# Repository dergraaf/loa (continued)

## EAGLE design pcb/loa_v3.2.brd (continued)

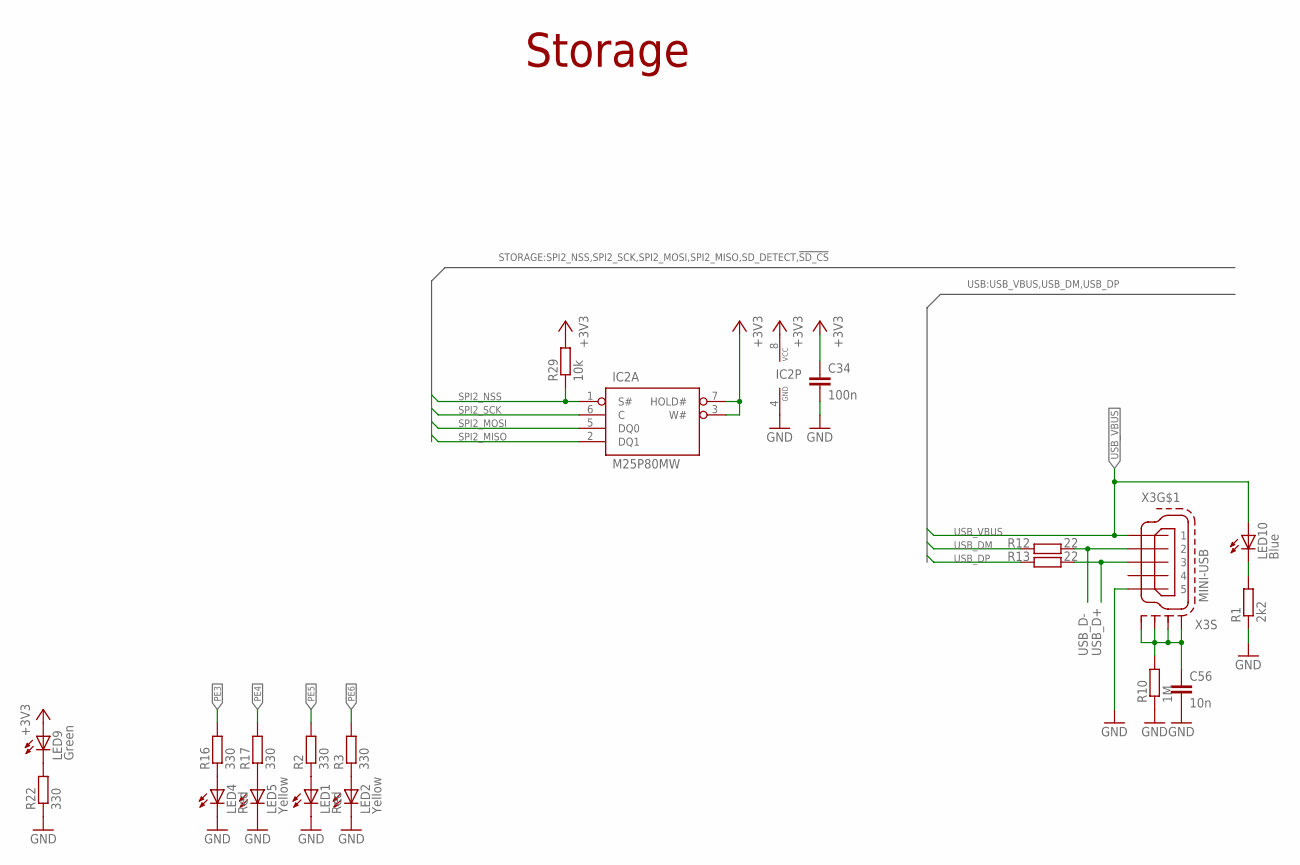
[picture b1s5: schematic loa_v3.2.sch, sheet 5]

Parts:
C34: 100n; C0603
C56: 10n; C0603
IC2: M25P80MW; SO-08M; DIGIKEY# M25P80-VMN6TPCT-ND
LED1, LED4: Red; CHIPLED_0805
LED2, LED5: Yellow; CHIPLED_0805
LED9: Green; CHIPLED_0805
LED10: Blue; CHIPLED_0805
R1: 2k2; R0805
R2, R3, R16, R17, R22: 330; R0603
R10: 1M; R0805
R12, R13: 22; R0603
R29: 10k; R0603
X3: MINI-USB; 32005-201

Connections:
+3V3: C34.1, IC2.3 (W#), IC2.7 (HOLD#), IC2.8 (VCC), LED9.A, R29.2; also elsewhere on the board
GND: C34.2, C56.2, IC2.4 (GND), LED1.C, LED2.C, LED4.C, LED5.C, R1.1, R10.1, R22.1, X3.5; also elsewhere on the board
unnamed: LED1.A, R2.1
unnamed: LED4.A, R16.1
unnamed: LED2.A, R3.1
unnamed: LED5.A, R17.1
unnamed: LED9.C, R22.2
unnamed: LED10.C, R1.2
unnamed: C56.1, R10.2, X3.M1 (S1), X3.M2 (S2), X3.M3 (S3), X3.M4 (S4)
PE3: R16.2; also elsewhere on the board
PE4: R17.2; also elsewhere on the board
PE5: R2.2; also elsewhere on the board
PE6: R3.2; also elsewhere on the board
SPI2_MISO: IC2.2 (DQ1); also elsewhere on the board
SPI2_MOSI: IC2.5 (DQ0); also elsewhere on the board
SPI2_NSS: IC2.1 (S#), R29.1; also elsewhere on the board
SPI2_SCK: IC2.6 (C); also elsewhere on the board
USB_D+: R13.2, X3.3; also elsewhere on the board
USB_D-: R12.2, X3.2; also elsewhere on the board
USB_DM: R12.1; also elsewhere on the board
USB_DP: R13.1; also elsewhere on the board
USB_VBUS: LED10.A, X3.1; also elsewhere on the board

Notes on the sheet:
Storage

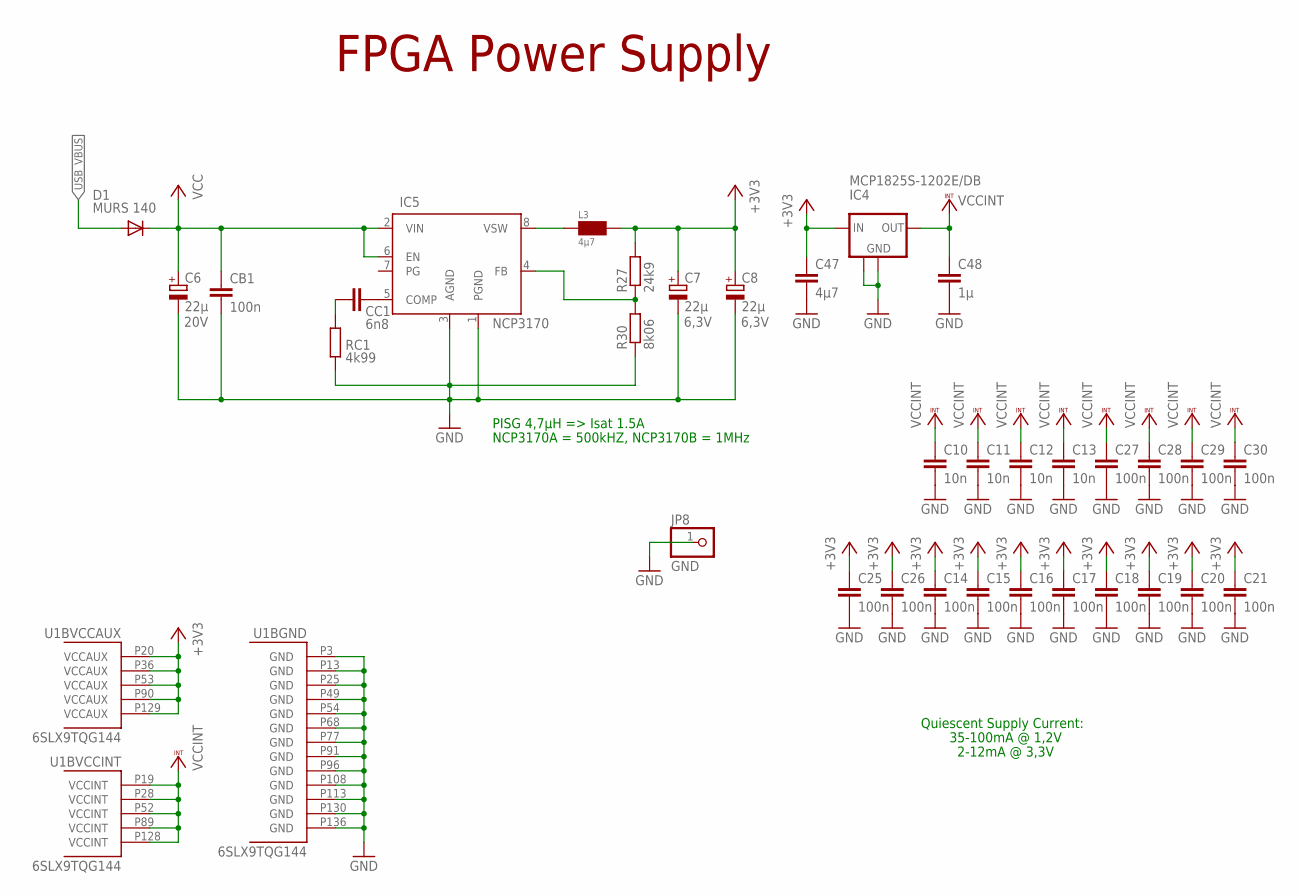
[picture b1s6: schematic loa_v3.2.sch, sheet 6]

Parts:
C6: 22µ; SMC_D; VOLTAGE 20V
C7, C8: 22µ; SMC_C; VOLTAGE 6,3V
C10, C11, C12, C13: 10n; C0603
C14, C15, C16, C17, C18, C19, C20, C21, C25, C26, C27, C28, C29, C30: 100n; C0603
C47: 4µ7; C0805
C48: 1µ; C0805
CB1: 100n; C0603
CC1: 6n8; C0805
D1: MURS 140; SMB
IC4: MCP1825S-1202E/DB; SOT223; DIGIKEY# MCP1825S-1202E/DB-ND
IC5: NCP3170; SO08; DIGIKEY# NCP3170ADR2GOSCT-ND
JP8: GND; 1X01
L3: 4µ7; L-PISG
R27: 24k9; M0805; DIGIKEY# 311-24.9KCRCT-ND
R30: 8k06; M0805; DIGIKEY# 311-8.06KCRCT-ND
RC1: 4k99; M0805; DIGIKEY# 311-4.99KCRCT-ND
U1: 6SLX9TQG144; TQ144; DIGIKEY# 122-1745-ND

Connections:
+3V3: C7.+, C8.+, C14.1, C15.1, C16.1, C17.1, C18.1, C19.1, C20.1, C21.1, C25.1, C26.1, C47.1, IC4.1 (IN), L3.2, R27.2, U1.P20 (VCCAUX), U1.P36 (VCCAUX), U1.P53 (VCCAUX), U1.P90 (VCCAUX), U1.P129 (VCCAUX); also elsewhere on the board
GND: C6.-, C7.-, C8.-, C10.2, C11.2, C12.2, C13.2, C14.2, C15.2, C16.2, C17.2, C18.2, C19.2, C20.2, C21.2, C25.2, C26.2, C27.2, C28.2, C29.2, C30.2, C47.2, C48.2, CB1.2, IC4.2 (GND), IC4.4 (GND), IC5.1 (PGND), IC5.3 (AGND), JP8.1, R30.1, RC1.1, U1.P3 (GND), U1.P13 (GND), U1.P25 (GND), U1.P49 (GND), U1.P54 (GND), U1.P68 (GND), U1.P77 (GND), U1.P91 (GND), U1.P96 (GND), U1.P108 (GND), U1.P113 (GND), U1.P130 (GND), U1.P136 (GND); also elsewhere on the board
unnamed: CC1.2, RC1.2
unnamed: CC1.1, IC5.5 (COMP)
unnamed: IC5.8 (VSW), L3.1
unnamed: IC5.4 (FB), R27.1, R30.2
USB_VBUS: D1.A; also elsewhere on the board
VCC: C6.+, CB1.1, D1.C, IC5.2 (VIN), IC5.6 (EN); also elsewhere on the board
VCCINT: C10.1, C11.1, C12.1, C13.1, C27.1, C28.1, C29.1, C30.1, C48.1, IC4.3 (OUT), U1.P19 (VCCINT), U1.P28 (VCCINT), U1.P52 (VCCINT), U1.P89 (VCCINT), U1.P128 (VCCINT)

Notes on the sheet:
35-100mA @ 1,2V
Quiescent Supply Current:
2-12mA @ 3,3V
FPGA Power Supply
PISG 4,7µH => Isat 1.5A
NCP3170A = 500kHZ, NCP3170B = 1MHz

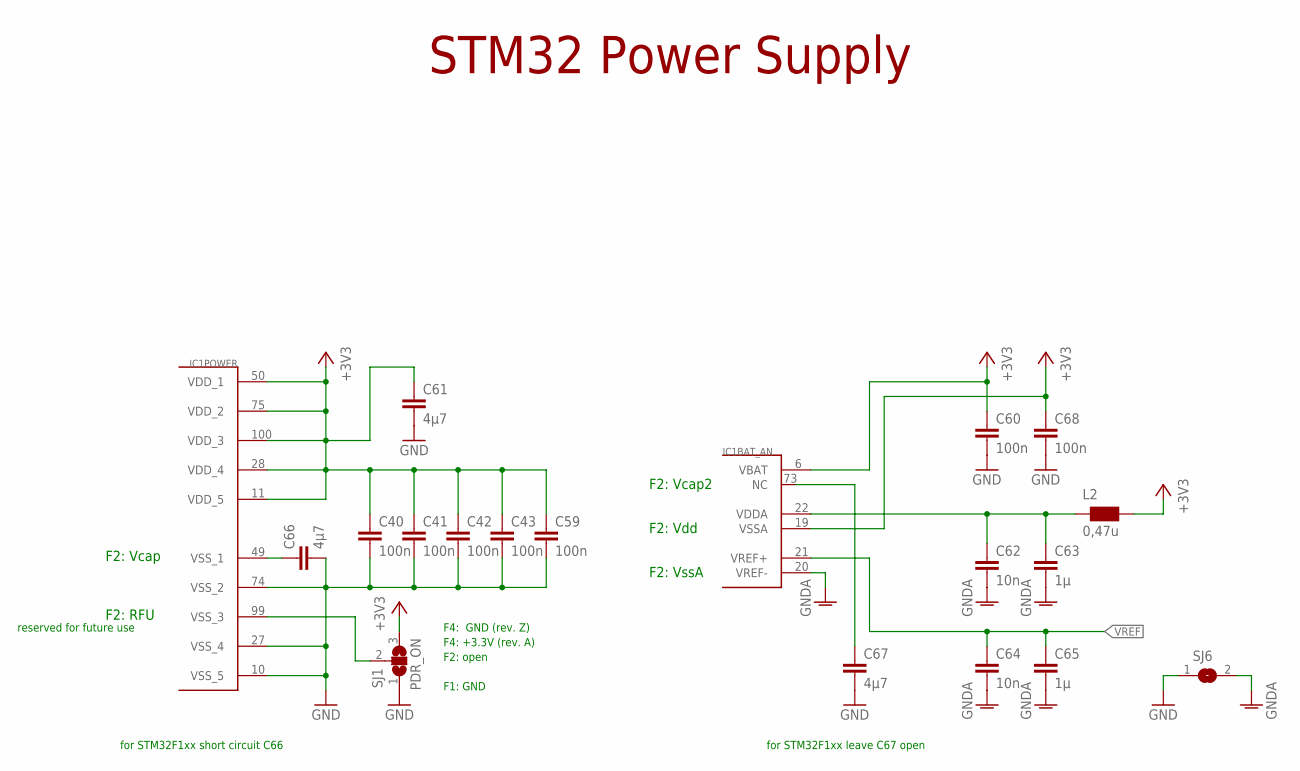
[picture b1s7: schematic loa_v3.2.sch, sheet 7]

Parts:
C40, C41, C42, C43, C59, C60, C68: 100n; C0603
C61, C66, C67: 4µ7; C0805
C62, C64: 10n; C0603
C63, C65: 1µ; C0805
IC1: STM32F10XVXT6; TQFP100; DIGIKEY# 497-11605-ND
L2: 0,47u; WE-KI_0805_B
SJ1: PDR_ON; SJ_2S
SJ6: SJS

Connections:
+3V3: C40.1, C41.1, C42.1, C43.1, C59.1, C60.1, C61.1, C68.1, IC1.6 (VBAT), IC1.11 (VDD_5), IC1.19 (VSSA), IC1.28 (VDD_4), IC1.50 (VDD_1), IC1.75 (VDD_2), IC1.100 (VDD_3), L2.1 (2), SJ1.3; also elsewhere on the board
GND: C40.2, C41.2, C42.2, C43.2, C59.2, C60.2, C61.2, C66.2, C67.2, C68.2, IC1.10 (VSS_5), IC1.27 (VSS_4), IC1.74 (VSS_2), SJ1.1, SJ6.1; also elsewhere on the board
GNDA: C62.2, C63.2, C64.2, C65.2, IC1.20 (VREF-), SJ6.2; also elsewhere on the board
unnamed: IC1.99 (VSS_3), SJ1.2
unnamed: C66.1, IC1.49 (VSS_1)
unnamed: C67.1, IC1.73 (NC)
VDDA: C62.1, C63.1, IC1.22 (VDDA), L2.2 (1)
VREF: C64.1, C65.1, IC1.21 (VREF+); also elsewhere on the board

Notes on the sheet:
F2: Vcap
F2: RFU
F2: Vdd
F2: VssA
F2: Vcap2
STM32 Power Supply
for STM32F1xx short circuit C66
reserved for future use
for STM32F1xx leave C67 open
F1: GND
F2: open
F4: +3.3V (rev. A)
F4: GND (rev. Z)

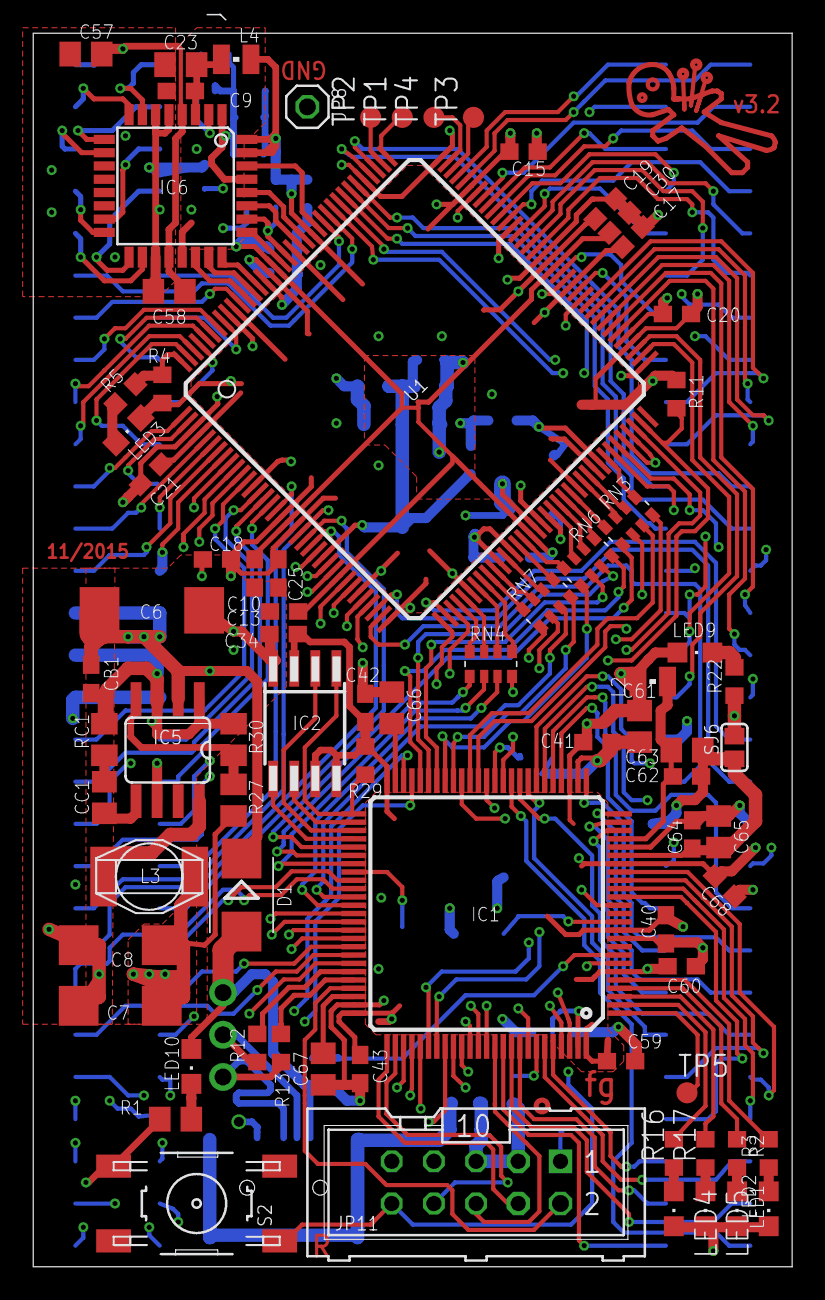
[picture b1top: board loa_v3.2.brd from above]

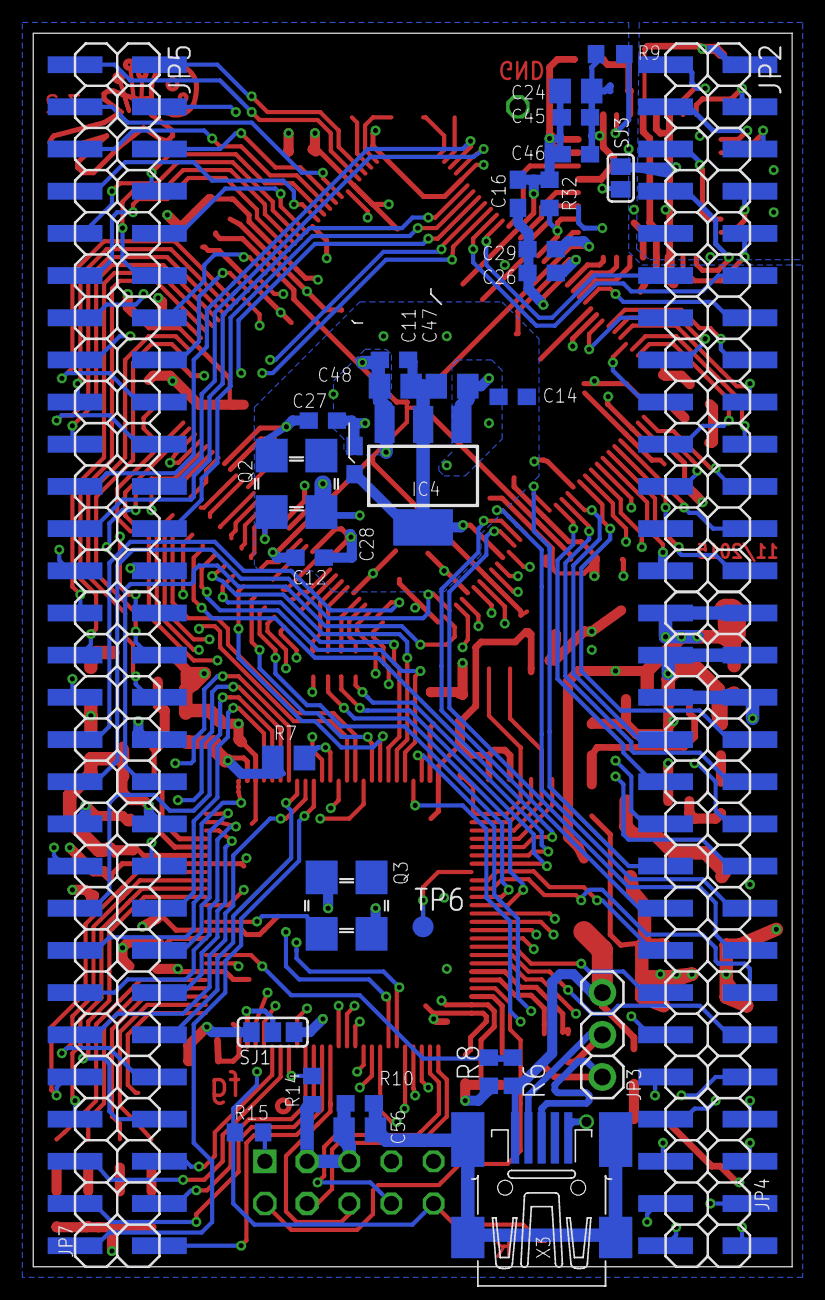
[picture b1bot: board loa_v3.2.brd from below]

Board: 4 copper layers, 45.7 x 74.3 mm, 112 parts (34 on the bottom side), 212 nets.

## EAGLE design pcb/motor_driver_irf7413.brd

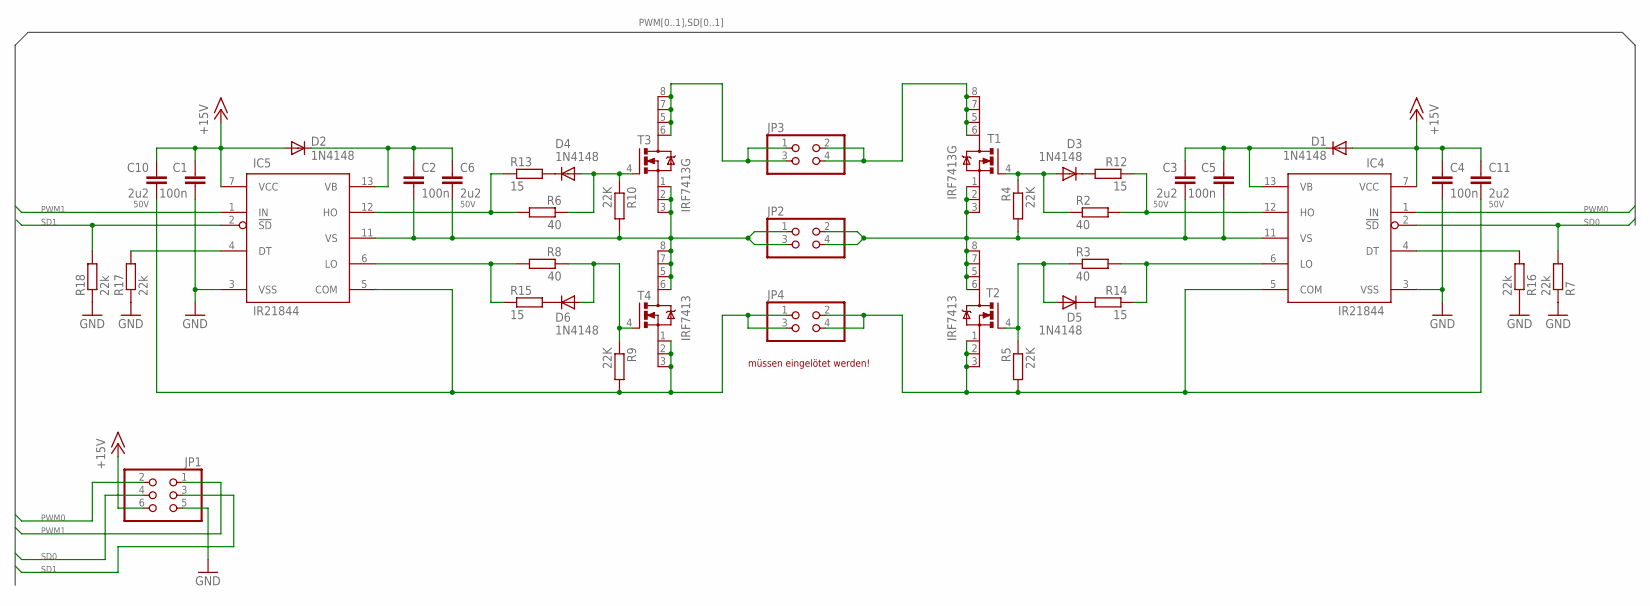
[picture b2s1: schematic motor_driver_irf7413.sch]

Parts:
C1, C4: 100n; C0805
C2, C5: 100n; C1206
C3, C6, C10, C11: 2u2; C1206; VOLTAGE 50V
D1, D2, D3, D4, D5, D6: 1N4148; SOD80C
IC4, IC5: IR21844; SO14
JP1: PINHD-2X3_2.54-SIDE; 2X03_SIDE
JP2, JP3, JP4: PINHD-2X2_2.54-SIDE; 2X02_SIDE
R2, R3, R6, R8: 40; M0805
R4, R5, R9, R10: 22K; M0805
R7, R16, R17, R18: 22k; M0805
R12, R13, R14, R15: 15; M0805
T1, T3: IRF7413G; SO08G
T2, T4: IRF7413; SO08

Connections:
+15V: C1.1, C4.1, C10.1, C11.1, D1.A, D2.A, IC4.7 (VCC), IC5.7 (VCC), JP1.6
DT0: IC4.4 (DT), R16.2
DT1: IC5.4 (DT), R17.2
GND: C1.2, C4.2, IC4.3 (VSS), IC5.3 (VSS), JP1.5, R7.1, R16.1, R17.1, R18.1
unnamed: C2.2, C6.2, IC5.11 (VS), JP2.1, JP2.3, R10.2, T3.1 (S), T3.2 (S1), T3.3 (S2), T4.5 (D), T4.6 (D1), T4.7 (D2), T4.8 (D3)
unnamed: C3.2, C5.2, IC4.11 (VS), JP2.2, JP2.4, R4.2, T1.1 (S), T1.2 (S1), T1.3 (S2), T2.5 (D), T2.6 (D1), T2.7 (D2), T2.8 (D3)
unnamed: D3.A, R2.1, R4.1, T1.4 (G)
unnamed: D4.A, R6.1, R10.1, T3.4 (G)
unnamed: IC4.12 (HO), R2.2, R12.1
unnamed: IC5.12 (HO), R6.2, R13.1
unnamed: IC5.6 (LO), R8.2, R15.1
unnamed: C2.1, C6.1, D2.C, IC5.13 (VB)
unnamed: D3.C, R12.2
unnamed: D6.A, R8.1, R9.1, T4.4 (G)
unnamed: D4.C, R13.2
unnamed: IC4.6 (LO), R3.2, R14.1
unnamed: D5.A, R3.1, R5.1, T2.4 (G)
unnamed: JP3.1, JP3.3, T3.5 (D), T3.6 (D1), T3.7 (D2), T3.8 (D3)
unnamed: D5.C, R14.2
unnamed: D6.C, R15.2
unnamed: JP3.2, JP3.4, T1.5 (D), T1.6 (D1), T1.7 (D2), T1.8 (D3)
unnamed: C10.2, IC5.5 (COM), JP4.1, JP4.3, R9.2, T4.1 (S), T4.2 (S1), T4.3 (S2)
unnamed: C11.2, IC4.5 (COM), JP4.2, JP4.4, R5.2, T2.1 (S), T2.2 (S1), T2.3 (S2)
unnamed: C3.1, C5.1, D1.C, IC4.13 (VB)
PWM0: IC4.1 (IN), JP1.2
PWM1: IC5.1 (IN), JP1.1
SD0: IC4.2 (!SD), JP1.4, R7.2
SD1: IC5.2 (!SD), JP1.3, R18.2

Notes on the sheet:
müssen eingelötet werden!

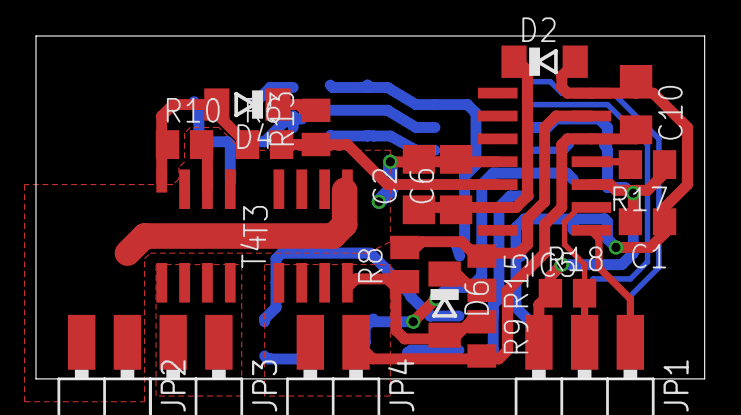
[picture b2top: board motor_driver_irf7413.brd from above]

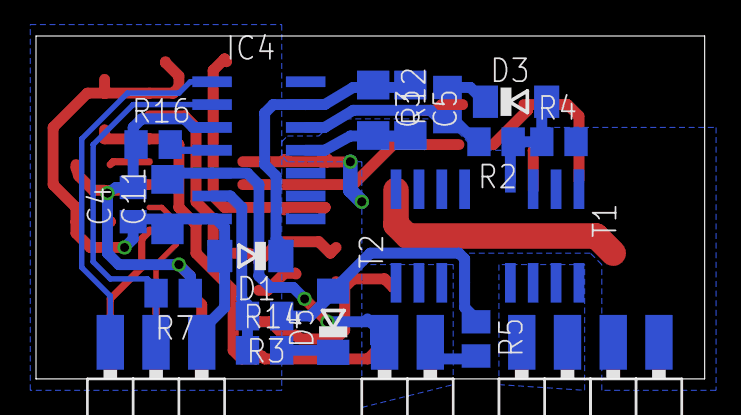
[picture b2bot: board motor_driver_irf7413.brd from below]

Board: 2 copper layers, 37.1 x 19.1 mm, 40 parts (18 on the bottom side), 28 nets.

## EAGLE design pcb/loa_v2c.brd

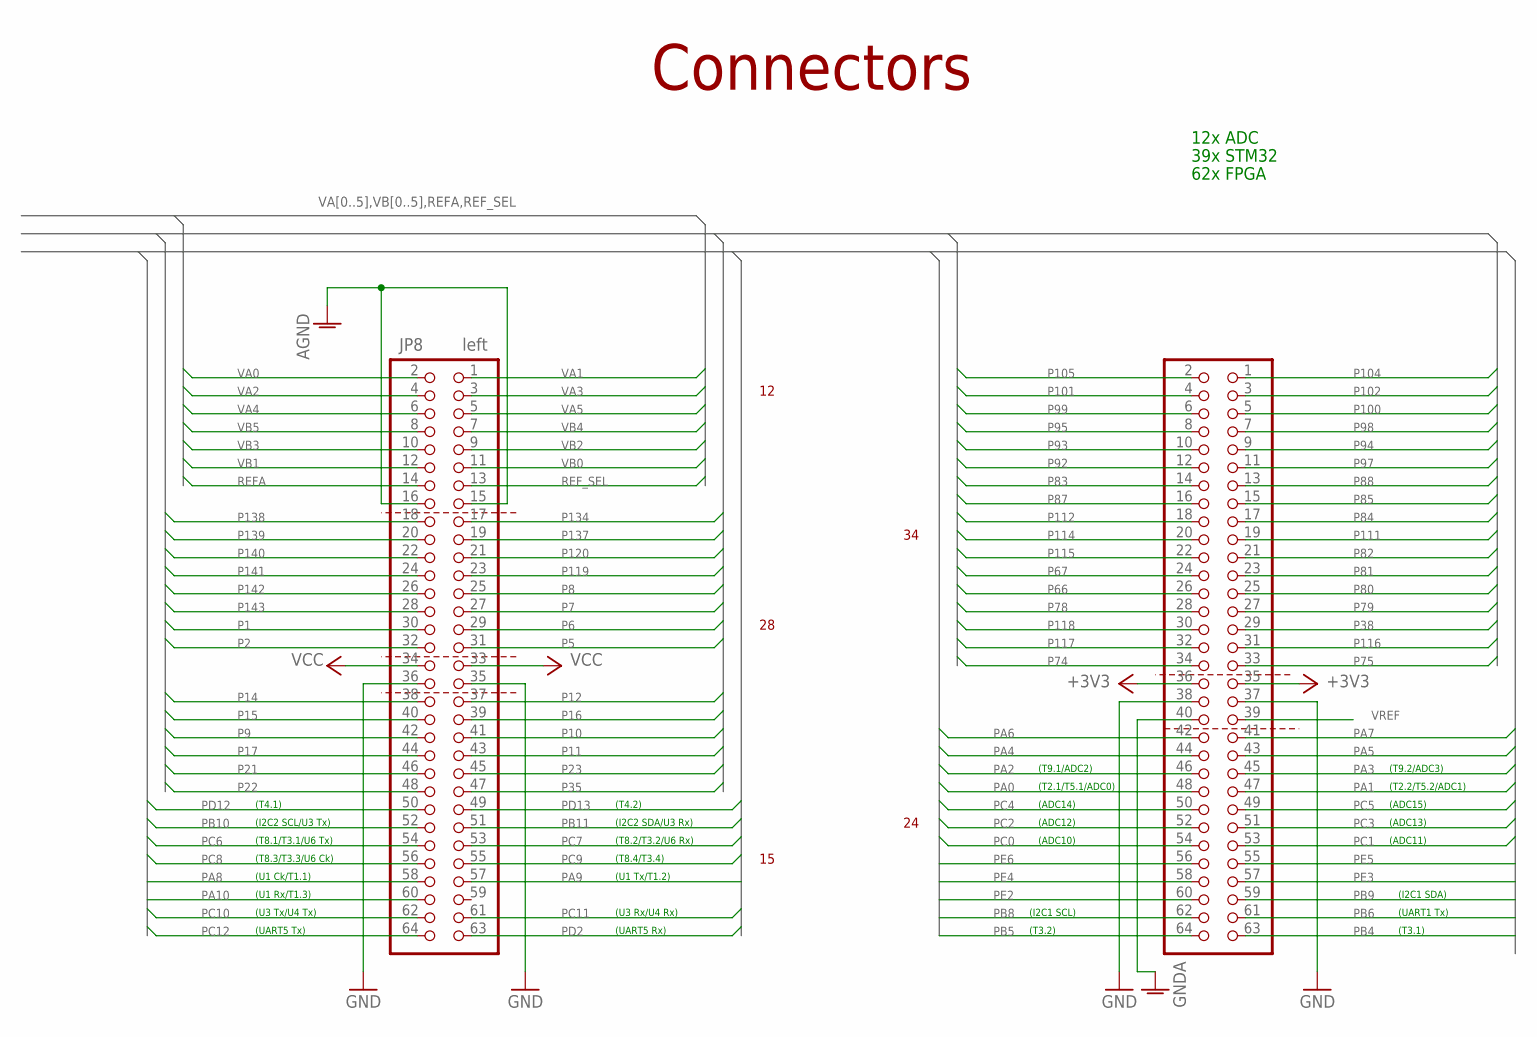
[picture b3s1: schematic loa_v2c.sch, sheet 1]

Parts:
JP7: right; 2X32M_SMD
JP8: left; 2X32M_SMD

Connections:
+3V3: JP7.35, JP7.36; also elsewhere on the board
AGND: JP8.15, JP8.16; also elsewhere on the board
GND: JP7.37, JP7.38, JP8.35, JP8.36; also elsewhere on the board
GNDA: JP7.40; also elsewhere on the board
P1: JP8.30; also elsewhere on the board
P2: JP8.32; also elsewhere on the board
P5: JP8.31; also elsewhere on the board
P6: JP8.29; also elsewhere on the board
P7: JP8.27; also elsewhere on the board
P8: JP8.25; also elsewhere on the board
P9: JP8.42; also elsewhere on the board
P10: JP8.41; also elsewhere on the board
P11: JP8.43; also elsewhere on the board
P12: JP8.37; also elsewhere on the board
P14: JP8.38; also elsewhere on the board
P15: JP8.40; also elsewhere on the board
P16: JP8.39; also elsewhere on the board
P17: JP8.44; also elsewhere on the board
P21: JP8.46; also elsewhere on the board
P22: JP8.48; also elsewhere on the board
P23: JP8.45; also elsewhere on the board
P35: JP8.47; also elsewhere on the board
P38: JP7.29; also elsewhere on the board
P66: JP7.26; also elsewhere on the board
P67: JP7.24; also elsewhere on the board
P74: JP7.34; also elsewhere on the board
P75: JP7.33; also elsewhere on the board
P78: JP7.28; also elsewhere on the board
P79: JP7.27; also elsewhere on the board
P80: JP7.25; also elsewhere on the board
P81: JP7.23; also elsewhere on the board
P82: JP7.21; also elsewhere on the board
P83: JP7.14; also elsewhere on the board
P84: JP7.17; also elsewhere on the board
P85: JP7.15; also elsewhere on the board
P87: JP7.16; also elsewhere on the board
P88: JP7.13; also elsewhere on the board
P92: JP7.12; also elsewhere on the board
P93: JP7.10; also elsewhere on the board
P94: JP7.9; also elsewhere on the board
P95: JP7.8; also elsewhere on the board
P97: JP7.11; also elsewhere on the board
P98: JP7.7; also elsewhere on the board
P99: JP7.6; also elsewhere on the board
P100: JP7.5; also elsewhere on the board
P101: JP7.4; also elsewhere on the board
P102: JP7.3; also elsewhere on the board
P104: JP7.1; also elsewhere on the board
P105: JP7.2; also elsewhere on the board
P111: JP7.19; also elsewhere on the board
P112: JP7.18; also elsewhere on the board
P114: JP7.20; also elsewhere on the board
P115: JP7.22; also elsewhere on the board
P116: JP7.31; also elsewhere on the board
P117: JP7.32; also elsewhere on the board
P118: JP7.30; also elsewhere on the board
P119: JP8.23; also elsewhere on the board
P120: JP8.21; also elsewhere on the board
P134: JP8.17; also elsewhere on the board
P137: JP8.19; also elsewhere on the board
P138: JP8.18; also elsewhere on the board
P139: JP8.20; also elsewhere on the board
P140: JP8.22; also elsewhere on the board
P141: JP8.24; also elsewhere on the board
P142: JP8.26; also elsewhere on the board
P143: JP8.28; also elsewhere on the board
PA0: JP7.48; also elsewhere on the board
PA1: JP7.47; also elsewhere on the board
PA2: JP7.46; also elsewhere on the board
PA3: JP7.45; also elsewhere on the board
PA4: JP7.44; also elsewhere on the board
PA5: JP7.43; also elsewhere on the board
PA6: JP7.42; also elsewhere on the board
PA7: JP7.41; also elsewhere on the board
PA8: JP8.58; also elsewhere on the board
PA9: JP8.57; also elsewhere on the board
PA10: JP8.60; also elsewhere on the board
PB4: JP7.63; also elsewhere on the board
PB5: JP7.64; also elsewhere on the board
PB6: JP7.61; also elsewhere on the board
PB8: JP7.62; also elsewhere on the board
PB9: JP7.59; also elsewhere on the board
PB10: JP8.52; also elsewhere on the board
PB11: JP8.51; also elsewhere on the board
PC0: JP7.54; also elsewhere on the board
PC1: JP7.53; also elsewhere on the board
PC2: JP7.52; also elsewhere on the board
PC3: JP7.51; also elsewhere on the board
PC4: JP7.50; also elsewhere on the board
PC5: JP7.49; also elsewhere on the board
PC6: JP8.54; also elsewhere on the board
PC7: JP8.53; also elsewhere on the board
PC8: JP8.56; also elsewhere on the board
PC9: JP8.55; also elsewhere on the board
PC10: JP8.62; also elsewhere on the board
PC11: JP8.61; also elsewhere on the board
PC12: JP8.64; also elsewhere on the board
PD2: JP8.63; also elsewhere on the board
PD12: JP8.50; also elsewhere on the board
PD13: JP8.49; also elsewhere on the board
PE2: JP7.60; also elsewhere on the board
PE3: JP7.57; also elsewhere on the board
PE4: JP7.58; also elsewhere on the board
PE5: JP7.55; also elsewhere on the board
PE6: JP7.56; also elsewhere on the board
REFA: JP8.14; also elsewhere on the board
REF_SEL: JP8.13; also elsewhere on the board
VA0: JP8.2; also elsewhere on the board
VA1: JP8.1; also elsewhere on the board
VA2: JP8.4; also elsewhere on the board
VA3: JP8.3; also elsewhere on the board
VA4: JP8.6; also elsewhere on the board
VA5: JP8.5; also elsewhere on the board
VB0: JP8.11; also elsewhere on the board
VB1: JP8.12; also elsewhere on the board
VB2: JP8.9; also elsewhere on the board
VB3: JP8.10; also elsewhere on the board
VB4: JP8.7; also elsewhere on the board
VB5: JP8.8; also elsewhere on the board
VCC: JP8.33, JP8.34; also elsewhere on the board
VREF: JP7.39; also elsewhere on the board

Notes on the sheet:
Connectors
(T2.1/T5.1/ADC0)
(T2.2/T5.2/ADC1)
(T9.1/ADC2)
(T9.2/ADC3)
(ADC10)
(ADC11)
(ADC12)
(ADC13)
(ADC14)
(ADC15)
(I2C1 SCL)
(I2C1 SDA)
(UART1 Tx)
(T3.1)
(T3.2)
(UART5 Rx)
(UART5 Tx)
(T8.1/T3.1/U6 Tx)
(T8.2/T3.2/U6 Rx)
(T8.3/T3.3/U6 Ck)
(T8.4/T3.4)
(T4.2)
(T4.1)
(U1 Tx/T1.2)
(U1 Rx/T1.3)
(U1 Ck/T1.1)
(U3 Tx/U4 Tx)
(U3 Rx/U4 Rx)
(I2C2 SDA/U3 Rx)
(I2C2 SCL/U3 Tx)
12x ADC
39x STM32
62x FPGA

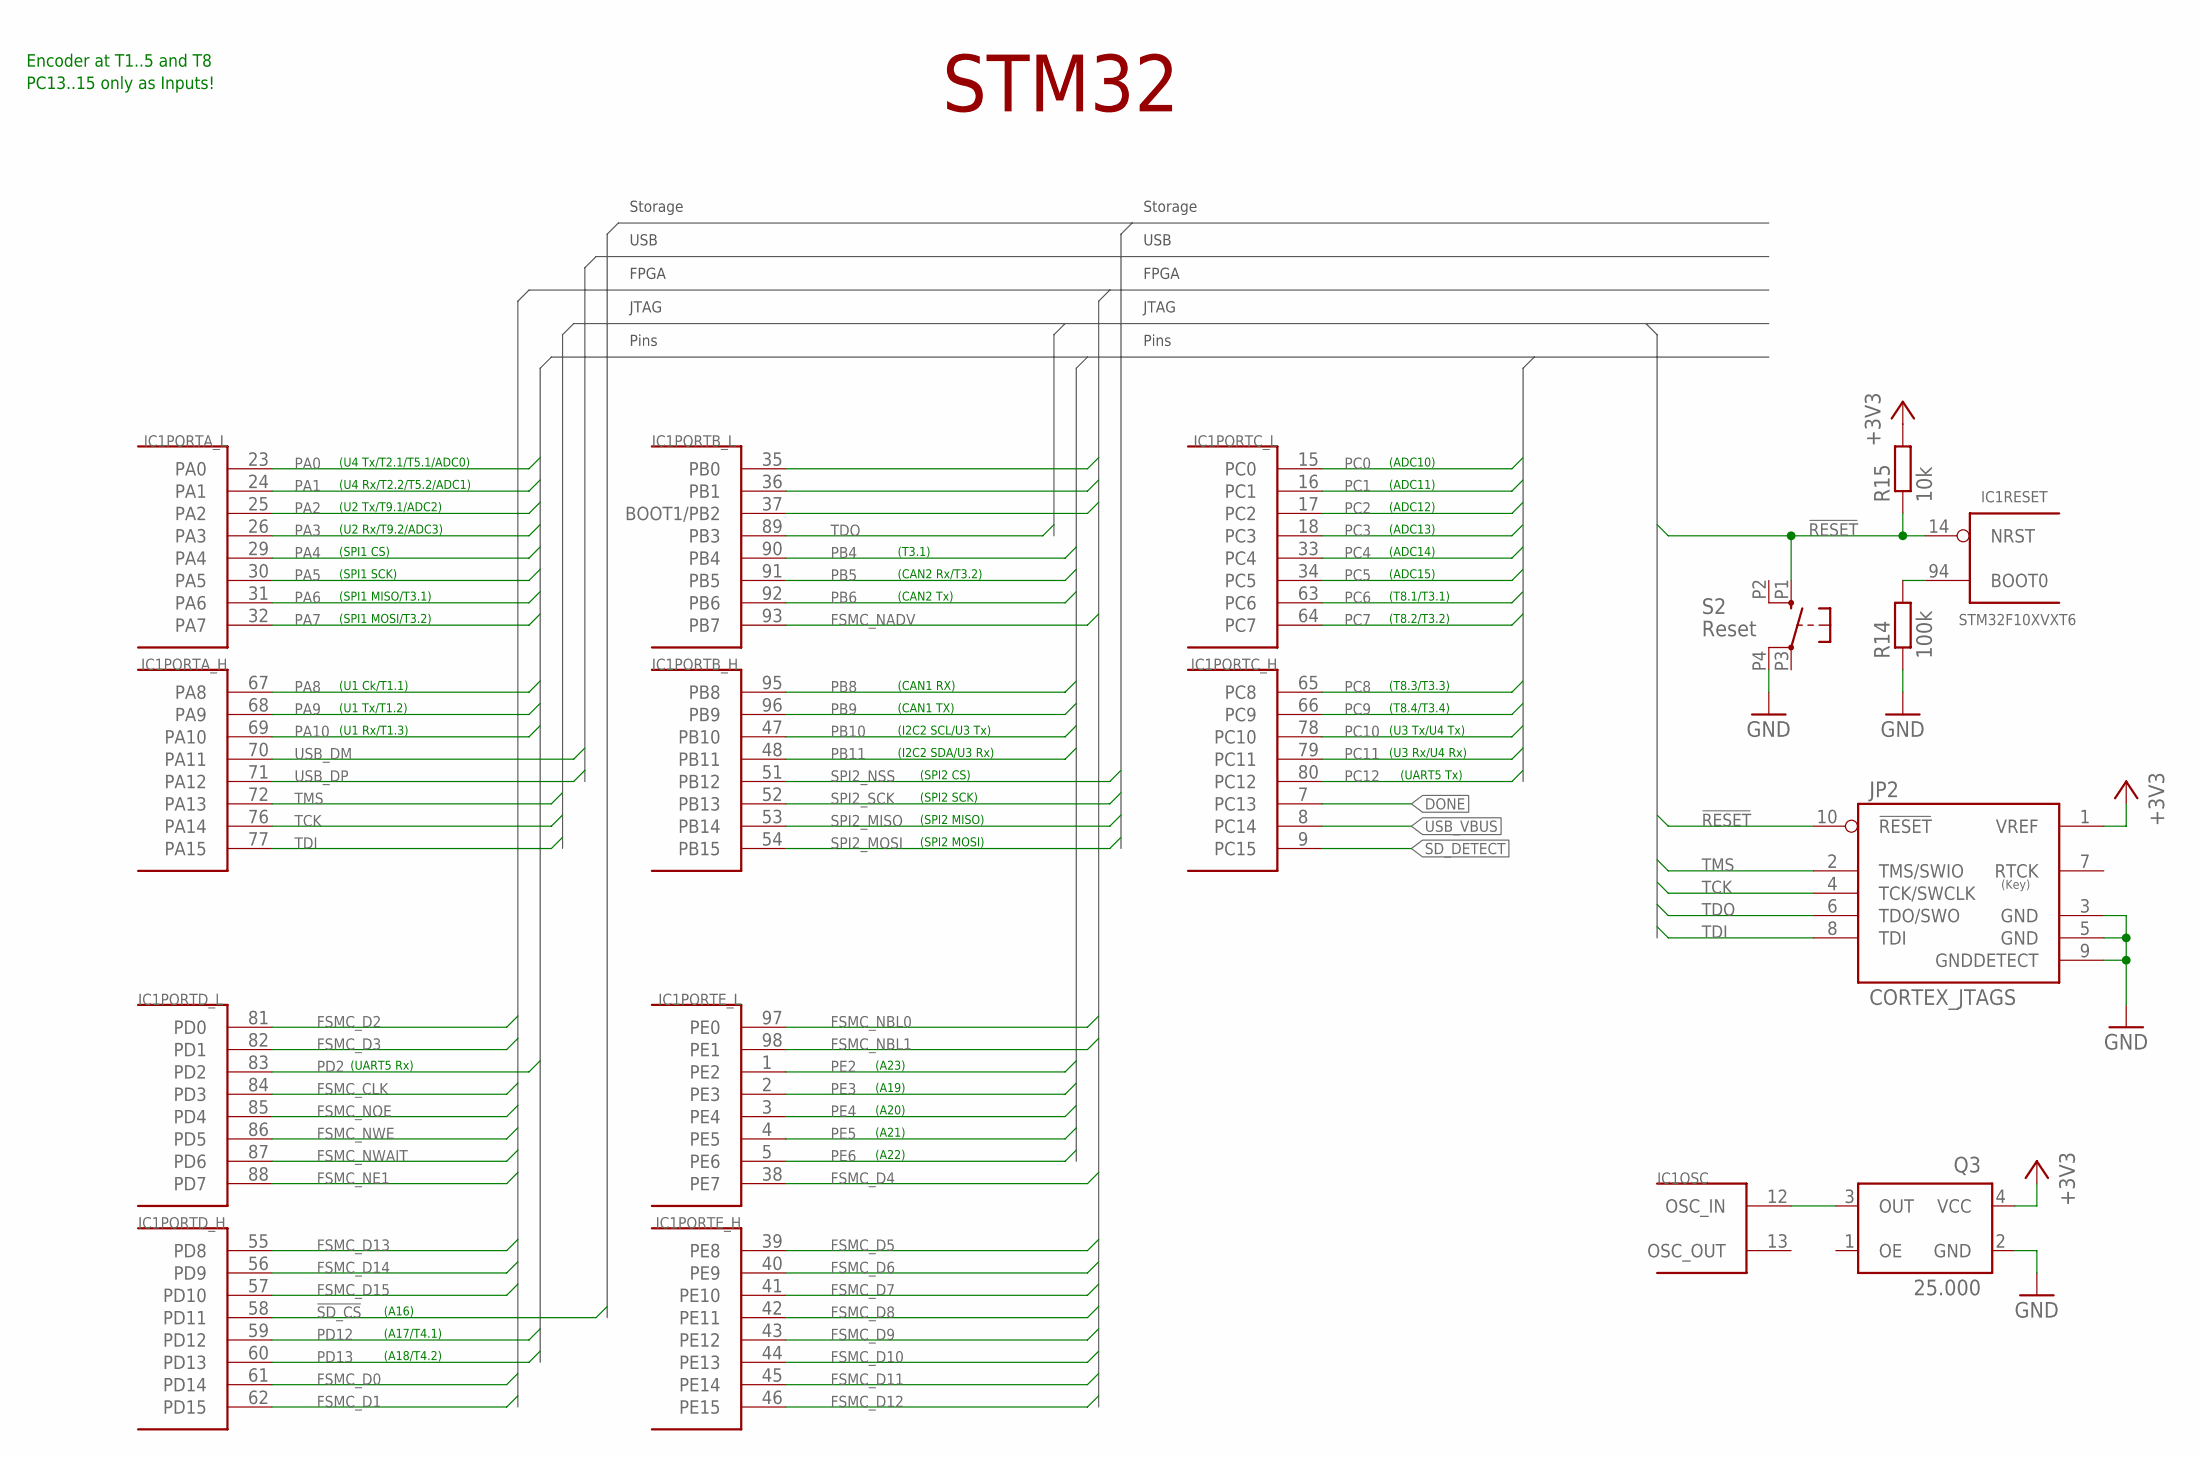
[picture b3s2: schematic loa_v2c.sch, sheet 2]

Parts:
IC1: STM32F10XVXT6; TQFP100
JP2: CORTEX_JTAGS; 2X05SMD
Q3: 25.000; XO53
R14: 100k; R0603
R15: 10k; R0603
S2: Reset; B3F-10XX-SMD

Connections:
!RESET: IC1.14 (NRST), JP2.10 (!RESET), R15.1, S2.P1 (S)
!SD_CS: IC1.58 (PD11); also elsewhere on the board
+3V3: JP2.1 (VREF), Q3.4 (VCC), R15.2; also elsewhere on the board
CCLK: IC1.35 (PB0); also elsewhere on the board
DONE: IC1.7 (PC13); also elsewhere on the board
FSMC_CLK: IC1.84 (PD3); also elsewhere on the board
FSMC_D0: IC1.61 (PD14); also elsewhere on the board
FSMC_D1: IC1.62 (PD15); also elsewhere on the board
FSMC_D2: IC1.81 (PD0); also elsewhere on the board
FSMC_D3: IC1.82 (PD1); also elsewhere on the board
FSMC_D4: IC1.38 (PE7); also elsewhere on the board
FSMC_D5: IC1.39 (PE8); also elsewhere on the board
FSMC_D6: IC1.40 (PE9); also elsewhere on the board
FSMC_D7: IC1.41 (PE10); also elsewhere on the board
FSMC_D8: IC1.42 (PE11); also elsewhere on the board
FSMC_D9: IC1.43 (PE12); also elsewhere on the board
FSMC_D10: IC1.44 (PE13); also elsewhere on the board
FSMC_D11: IC1.45 (PE14); also elsewhere on the board
FSMC_D12: IC1.46 (PE15); also elsewhere on the board
FSMC_D13: IC1.55 (PD8); also elsewhere on the board
FSMC_D14: IC1.56 (PD9); also elsewhere on the board
FSMC_D15: IC1.57 (PD10); also elsewhere on the board
FSMC_NADV: IC1.93 (PB7); also elsewhere on the board
FSMC_NBL0: IC1.97 (PE0); also elsewhere on the board
FSMC_NBL1: IC1.98 (PE1); also elsewhere on the board
FSMC_NE1: IC1.88 (PD7); also elsewhere on the board
FSMC_NOE: IC1.85 (PD4); also elsewhere on the board
FSMC_NWAIT: IC1.87 (PD6); also elsewhere on the board
FSMC_NWE: IC1.86 (PD5); also elsewhere on the board
GND: JP2.3 (GND), JP2.5 (GND), JP2.9 (GNDDETECT), Q3.2 (GND), R14.1, S2.P4 (P1); also elsewhere on the board
INIT_B: IC1.36 (PB1); also elsewhere on the board
unnamed: IC1.94 (BOOT0), R14.2
unnamed: IC1.12 (OSC_IN), Q3.3 (OUT)
PA0: IC1.23 (PA0); also elsewhere on the board
PA1: IC1.24 (PA1); also elsewhere on the board
PA2: IC1.25 (PA2); also elsewhere on the board
PA3: IC1.26 (PA3); also elsewhere on the board
PA4: IC1.29 (PA4); also elsewhere on the board
PA5: IC1.30 (PA5); also elsewhere on the board
PA6: IC1.31 (PA6); also elsewhere on the board
PA7: IC1.32 (PA7); also elsewhere on the board
PA8: IC1.67 (PA8); also elsewhere on the board
PA9: IC1.68 (PA9); also elsewhere on the board
PA10: IC1.69 (PA10); also elsewhere on the board
PB4: IC1.90 (PB4); also elsewhere on the board
PB5: IC1.91 (PB5); also elsewhere on the board
PB6: IC1.92 (PB6); also elsewhere on the board
PB8: IC1.95 (PB8); also elsewhere on the board
PB9: IC1.96 (PB9); also elsewhere on the board
PB10: IC1.47 (PB10); also elsewhere on the board
PB11: IC1.48 (PB11); also elsewhere on the board
PC0: IC1.15 (PC0); also elsewhere on the board
PC1: IC1.16 (PC1); also elsewhere on the board
PC2: IC1.17 (PC2); also elsewhere on the board
PC3: IC1.18 (PC3); also elsewhere on the board
PC4: IC1.33 (PC4); also elsewhere on the board
PC5: IC1.34 (PC5); also elsewhere on the board
PC6: IC1.63 (PC6); also elsewhere on the board
PC7: IC1.64 (PC7); also elsewhere on the board
PC8: IC1.65 (PC8); also elsewhere on the board
PC9: IC1.66 (PC9); also elsewhere on the board
PC10: IC1.78 (PC10); also elsewhere on the board
PC11: IC1.79 (PC11); also elsewhere on the board
PC12: IC1.80 (PC12); also elsewhere on the board
PD2: IC1.83 (PD2); also elsewhere on the board
PD12: IC1.59 (PD12); also elsewhere on the board
PD13: IC1.60 (PD13); also elsewhere on the board
PE2: IC1.1 (PE2); also elsewhere on the board
PE3: IC1.2 (PE3); also elsewhere on the board
PE4: IC1.3 (PE4); also elsewhere on the board
PE5: IC1.4 (PE5); also elsewhere on the board
PE6: IC1.5 (PE6); also elsewhere on the board
PROGRAM_B: IC1.37 (BOOT1/PB2); also elsewhere on the board
SD_DETECT: IC1.9 (PC15); also elsewhere on the board
SPI2_MISO: IC1.53 (PB14); also elsewhere on the board
SPI2_MOSI: IC1.54 (PB15); also elsewhere on the board
SPI2_NSS: IC1.51 (PB12); also elsewhere on the board
SPI2_SCK: IC1.52 (PB13); also elsewhere on the board
TCK: IC1.76 (PA14), JP2.4 (TCK/SWCLK)
TDI: IC1.77 (PA15), JP2.8 (TDI)
TDO: IC1.89 (PB3), JP2.6 (TDO/SWO)
TMS: IC1.72 (PA13), JP2.2 (TMS/SWIO)
USB_DM: IC1.70 (PA11); also elsewhere on the board
USB_DP: IC1.71 (PA12); also elsewhere on the board
USB_VBUS: IC1.8 (PC14); also elsewhere on the board

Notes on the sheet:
(U4 Tx/T2.1/T5.1/ADC0)
(U4 Rx/T2.2/T5.2/ADC1)
(U2 Tx/T9.1/ADC2)
(U2 Rx/T9.2/ADC3)
(T3.1)
(CAN2 Rx/T3.2)
(CAN1 RX)
(CAN1 TX)
(I2C2 SDA/U3 Rx)
(I2C2 SCL/U3 Tx)
(CAN2 Tx)
(U3 Tx/U4 Tx)
(U3 Rx/U4 Rx)
(UART5 Rx)
STM32
Encoder at T1..5 and T8
(ADC10)
(ADC11)
(ADC12)
(ADC13)
(ADC14)
(ADC15)
(T8.1/T3.1)
(T8.2/T3.2)
(T8.3/T3.3)
(T8.4/T3.4)
PC13..15 only as Inputs!
(UART5 Tx)
(A18/T4.2)
(A17/T4.1)
(A16)
(A23)
(A19)
(A20)
(A21)
(A22)
(U1 Tx/T1.2)
(U1 Rx/T1.3)
(SPI1 CS)
(SPI1 SCK)
